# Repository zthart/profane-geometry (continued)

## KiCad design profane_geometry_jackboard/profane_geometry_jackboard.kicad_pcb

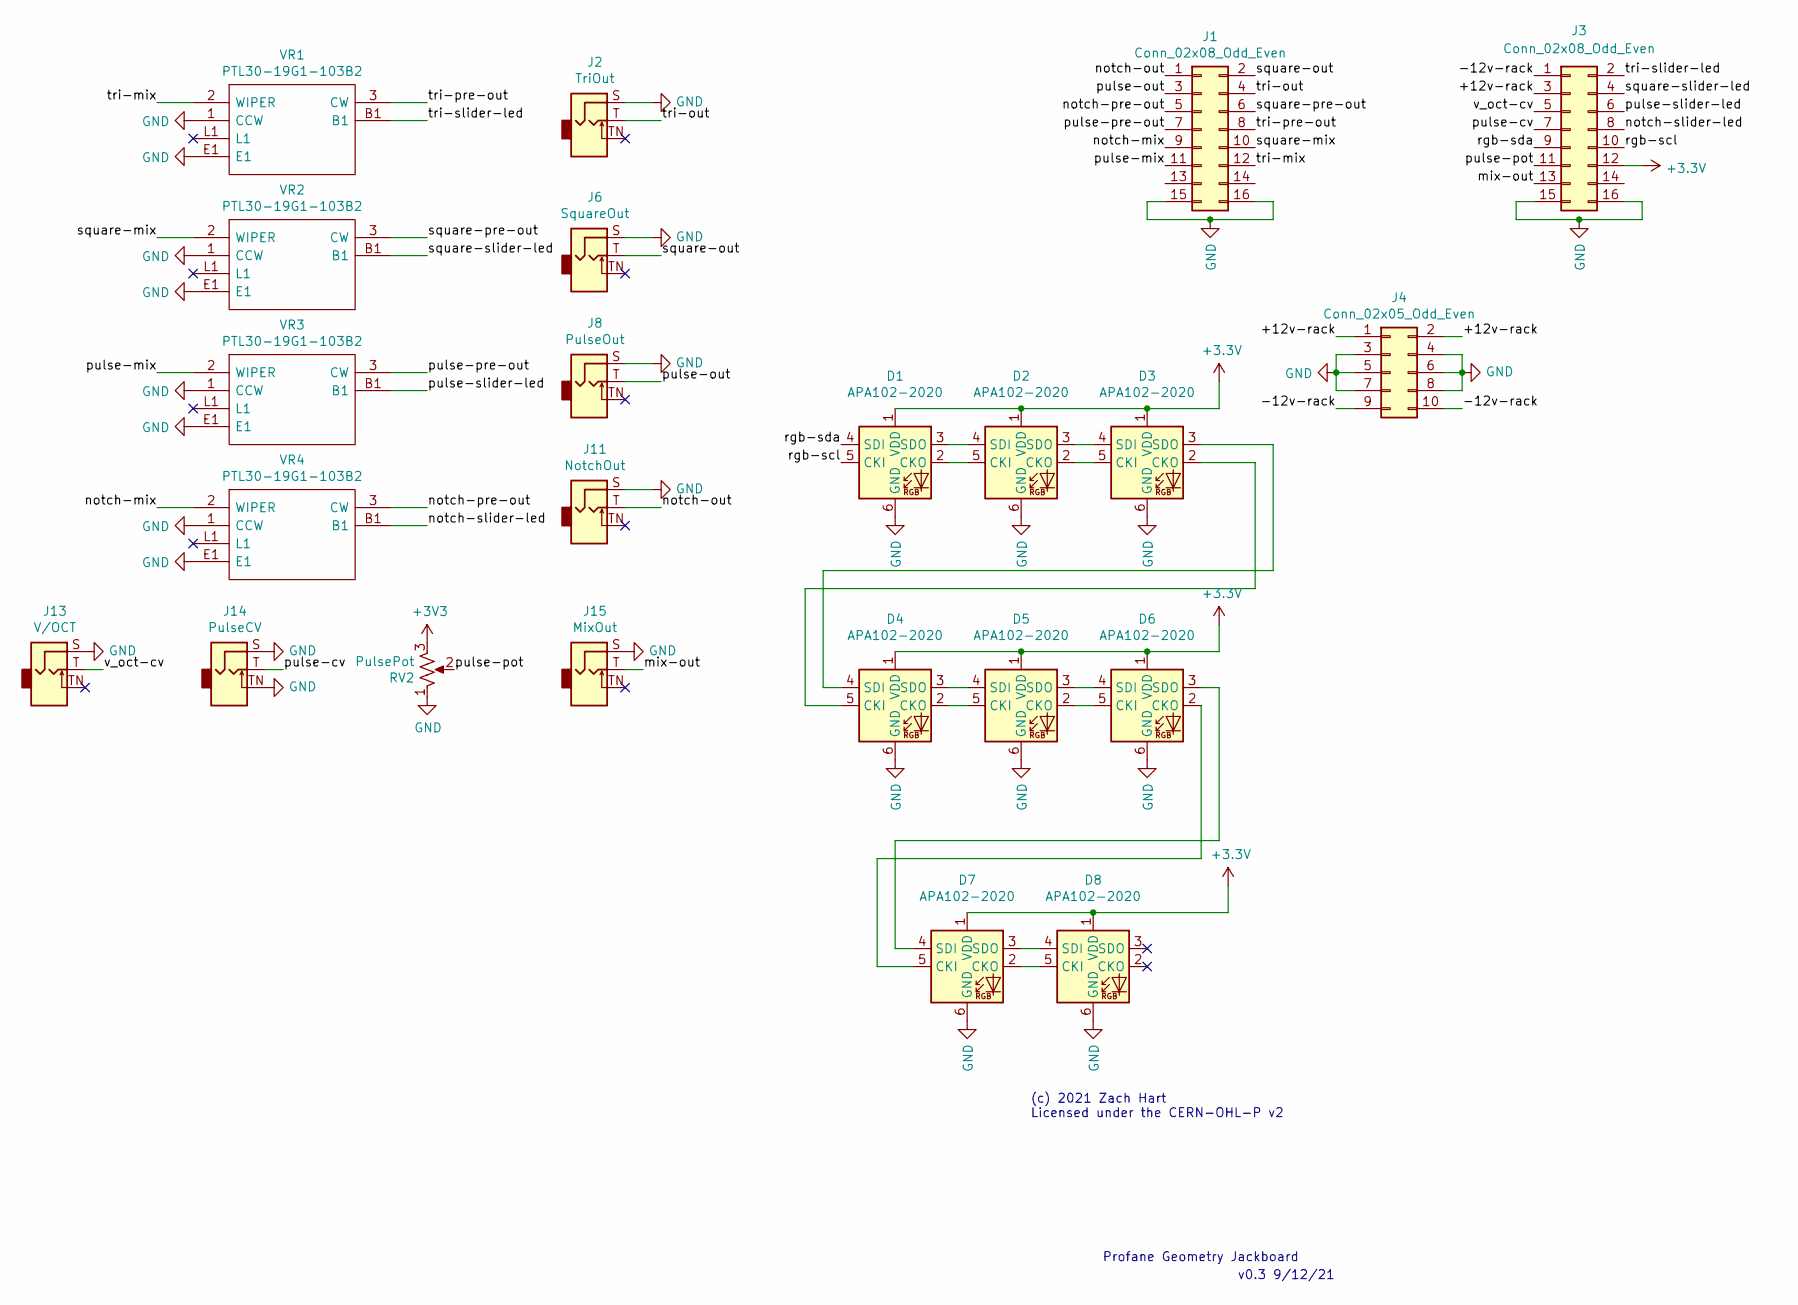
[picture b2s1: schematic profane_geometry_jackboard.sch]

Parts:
D1, D2, D3, D4, D5, D6, D7, D8: APA102-2020; LED-APA102-2020
J1, J3: Conn_02x08_Odd_Even; PinSocket_2x08_P2.54mm_Vertical
J2: TriOut; Jack_3.5mm_QingPu_WQP-PJ301BM_Vertical
J4: Conn_02x05_Odd_Even; PinHeader_2x05_P2.54mm_Vertical
J6: SquareOut; Jack_3.5mm_QingPu_WQP-PJ301BM_Vertical
J8: PulseOut; Jack_3.5mm_QingPu_WQP-PJ301BM_Vertical
J11: NotchOut; Jack_3.5mm_QingPu_WQP-PJ301BM_Vertical
J13: V/OCT; Jack_3.5mm_QingPu_WQP-PJ301BM_Vertical
J14: PulseCV; Jack_3.5mm_QingPu_WQP-PJ301BM_Vertical
J15: MixOut; Jack_3.5mm_QingPu_WQP-PJ301BM_Vertical
RV2: PulsePot; Potentiometer_TT_P0915N
VR1, VR2, VR3, VR4: PTL30-19G1-103B2; Slider_Potentiometer_Bourns_PTL_30mm; Mouser Part Number 652-PTL30-19G1-103B2

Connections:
/+12v-rack: J3.3, J4.1, J4.2
/-12v-rack: J3.1, J4.9, J4.10
/mix-out: J3.13, J15.T
/notch-mix: J1.9, VR4.2 (WIPER)
/notch-out: J1.1, J11.T
/notch-pre-out: J1.5, VR4.3 (CW)
/notch-slider-led: J3.8, VR4.B1
/pulse-cv: J3.7, J14.T
/pulse-mix: J1.11, VR3.2 (WIPER)
/pulse-out: J1.3, J8.T
/pulse-pot: J3.11, RV2.2
/pulse-pre-out: J1.7, VR3.3 (CW)
/pulse-slider-led: J3.6, VR3.B1
/rgb-scl: D1.5 (CKI), J3.10
/rgb-sda: D1.4 (SDI), J3.9
/square-mix: J1.10, VR2.2 (WIPER)
/square-out: J1.2, J6.T
/square-pre-out: J1.6, VR2.3 (CW)
/square-slider-led: J3.4, VR2.B1
/tri-mix: J1.12, VR1.2 (WIPER)
/tri-out: J1.4, J2.T
/tri-pre-out: J1.8, VR1.3 (CW)
/tri-slider-led: J3.2, VR1.B1
/v_oct-cv: J3.5, J13.T
GND: D1.6 (GND), D2.6 (GND), D3.6 (GND), D4.6 (GND), D5.6 (GND), D6.6 (GND), D7.6 (GND), D8.6 (GND), J1.15, J1.16, J2.S, J3.15, J3.16, J4.3, J4.4, J4.5, J4.6, J4.7, J4.8, J6.S, J8.S, J11.S, J13.S, J14.S, J14.TN, J15.S, RV2.1, VR1.1 (CCW), VR1.E1, VR2.1 (CCW), VR2.E1, VR3.1 (CCW), VR3.E1, VR4.1 (CCW), VR4.E1
unnamed: D1.2 (CKO), D2.5 (CKI)
unnamed: D1.3 (SDO), D2.4 (SDI)
unnamed: D2.2 (CKO), D3.5 (CKI)
unnamed: D2.3 (SDO), D3.4 (SDI)
unnamed: D3.2 (CKO), D4.5 (CKI)
unnamed: D3.3 (SDO), D4.4 (SDI)
unnamed: D4.2 (CKO), D5.5 (CKI)
unnamed: D4.3 (SDO), D5.4 (SDI)
unnamed: D5.2 (CKO), D6.5 (CKI)
unnamed: D5.3 (SDO), D6.4 (SDI)
unnamed: D6.2 (CKO), D7.5 (CKI)
unnamed: D6.3 (SDO), D7.4 (SDI)
unnamed: D7.2 (CKO), D8.5 (CKI)
unnamed: D7.3 (SDO), D8.4 (SDI)

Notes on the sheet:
Profane Geometry Jackboard
(c) 2021 Zach Hart Licensed under the CERN-OHL-P v2
v0.3 9/12/21

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
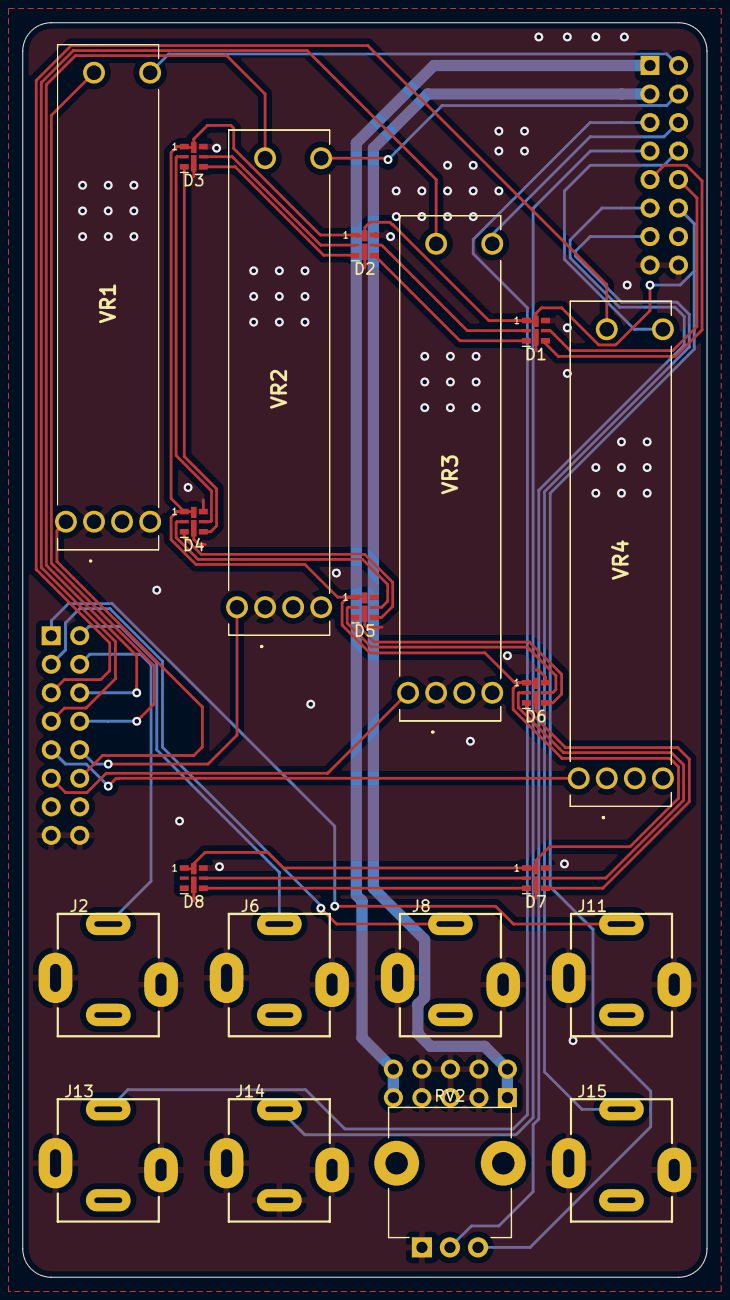
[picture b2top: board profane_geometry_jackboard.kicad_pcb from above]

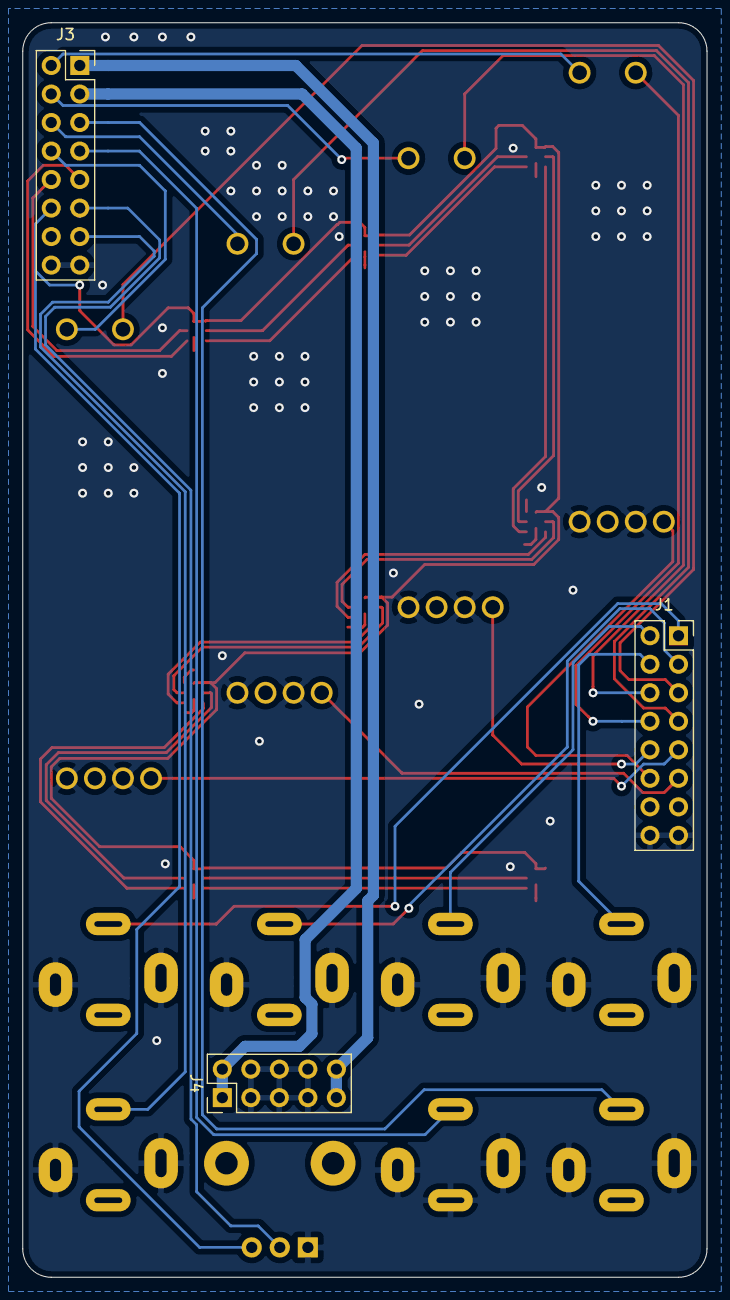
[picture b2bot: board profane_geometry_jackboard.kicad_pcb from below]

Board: 2 copper layers, 61.0 x 111.8 mm, 23 parts (3 on the bottom side), 40 nets.

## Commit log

2021-05-29 Add some basic testing firmware, no real functionality
2021-05-29 fix license links
2021-05-30 Sample single channel DAC write, use pulse pot as pitch input
2021-05-31 Clean up some testing code/types/errors
2021-06-03 Testing out basic Adc implementation, need to figure out interrupts
2021-06-10 ADC builder and what not, broken DynPin stuff
2021-06-14 Now we're cooking with interrupts
2021-06-17 Move dac stuff to hw/mcp4728
2021-11-29 some comments, formatting
2021-11-29 update .gitignore, current kicad project
2021-11-29 update things to gpio v2
2021-11-30 reorganize firmwar directory, add bsp
2021-11-30 fix old bsp reference
2021-11-30 Cleanup and docs for profane_geometry_bsp
    BSP Changes:
    - Updated the alias for the PWM CV input from `PwmCV` to `PwmCv` so that the
    generated `DynPinId` and `DynPinMode` constants would look a bit nicer.
    - Added frontpage docs for the bsp
    - Added license info to the Cargo.toml
    Firmware Changes:
2021-12-01 Debugger tooling and firmware updates
    Firmware:
    - Tweaks to the firmware to be able to reach the main event loop when
    running on the actual hardware
    - Set up clocks with the internal 32KHz oscillator, rather than a
    non-existent external oscillator.
    - Fix an off-by-one error in the ADC channel sweep logic
